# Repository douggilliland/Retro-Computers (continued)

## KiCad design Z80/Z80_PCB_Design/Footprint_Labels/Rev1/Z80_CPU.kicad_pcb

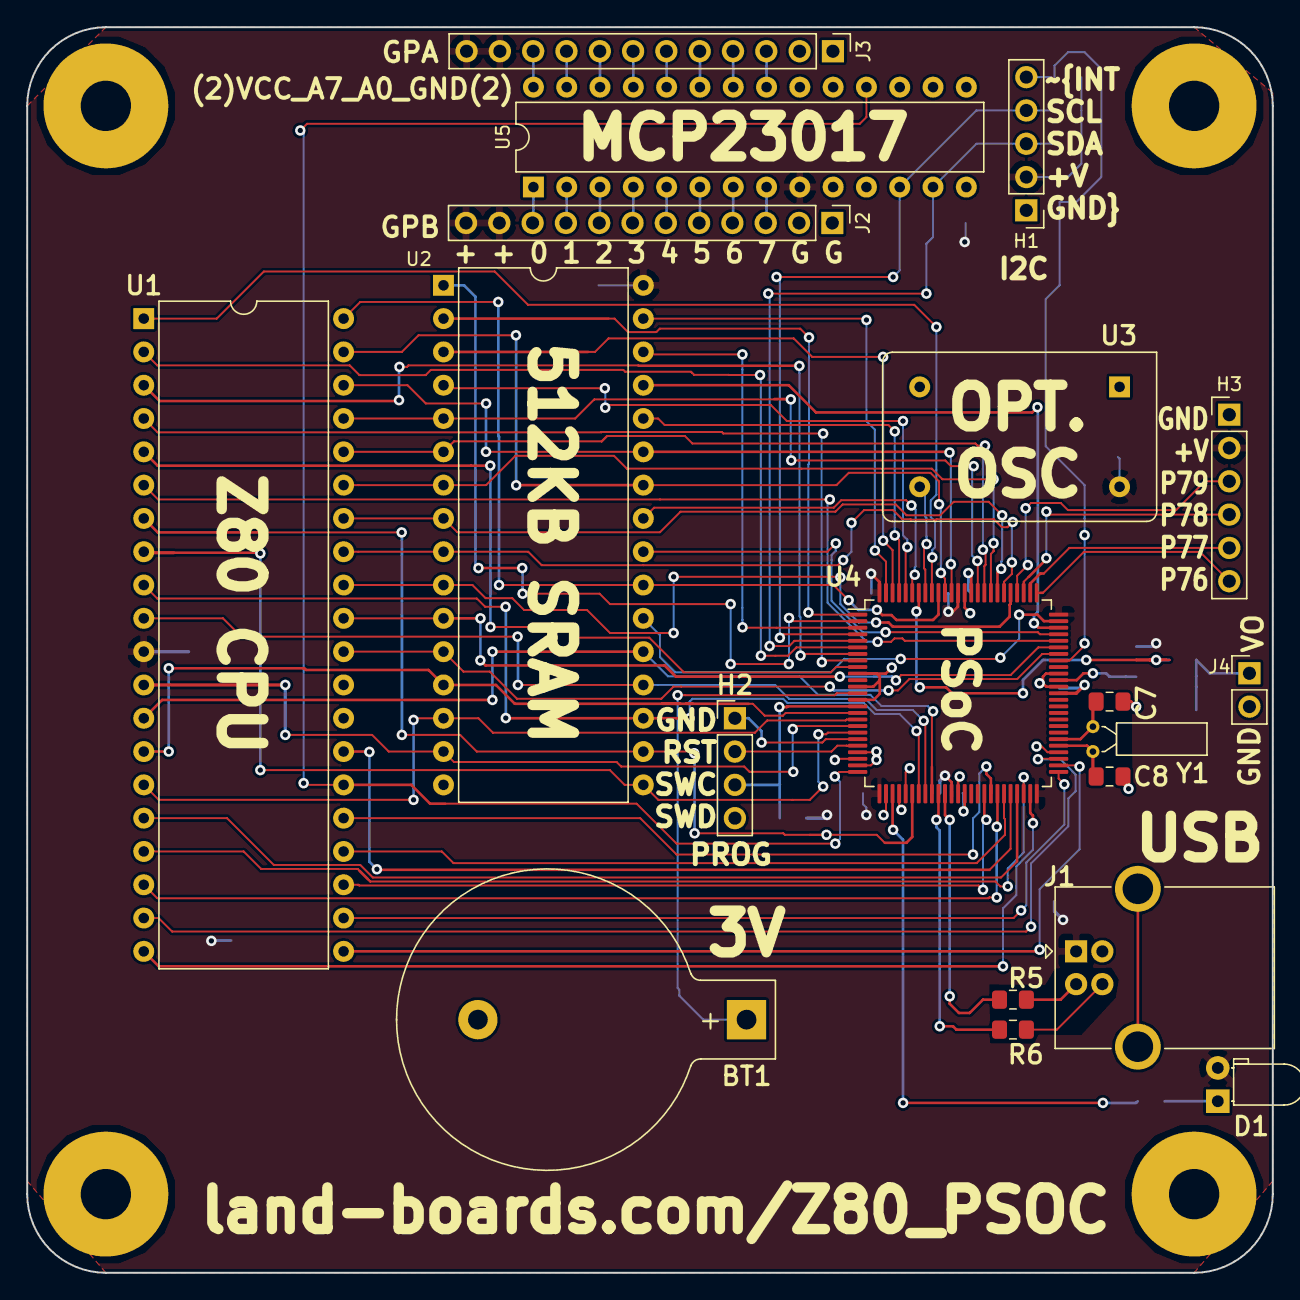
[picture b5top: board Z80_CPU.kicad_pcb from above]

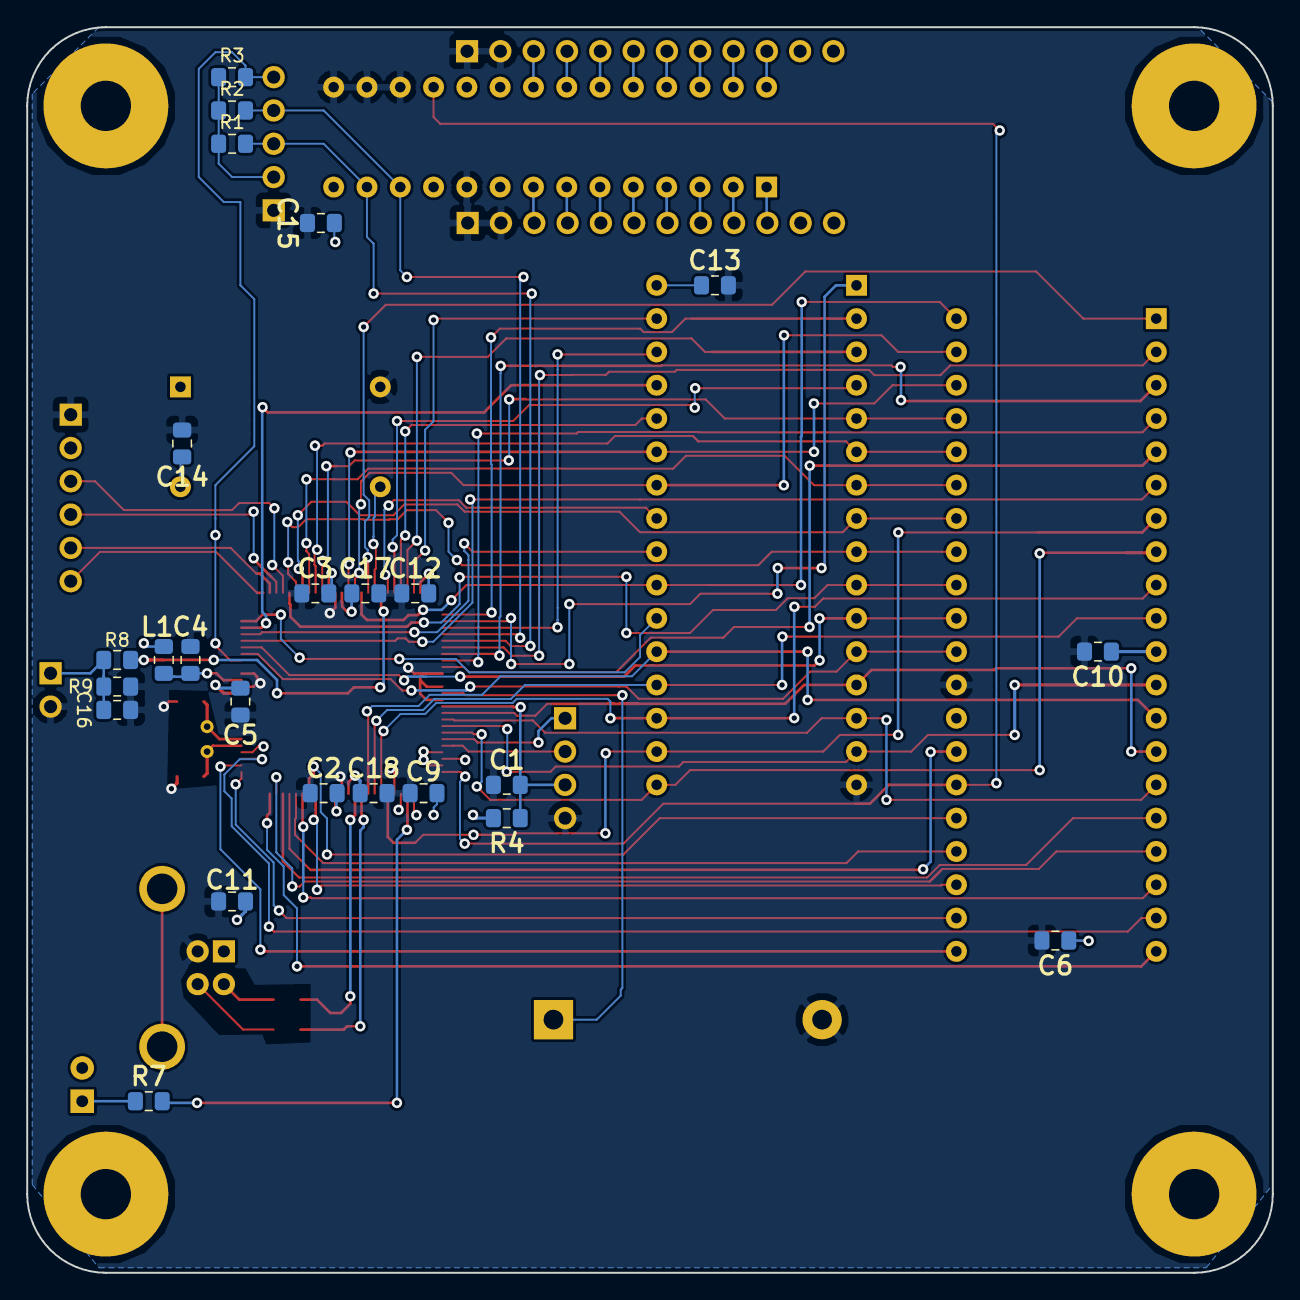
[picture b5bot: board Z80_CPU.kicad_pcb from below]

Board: 2 copper layers, 95.0 x 95.0 mm, 47 parts (24 on the bottom side), 92 nets.

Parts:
BT1: Battery_Cell; BatteryHolder_Keystone_103_1x20mm
C1, C6, C9, C10, C11, C12, C13, C14, C15, C17, C18: 0.1uF; C_0805_2012Metric_Pad1.15x1.40mm_HandSolder
C2, C3, C4, C5: 1uF; C_0805_2012Metric_Pad1.15x1.40mm_HandSolder
C7, C8, C16: 10pF; C_0805_2012Metric_Pad1.15x1.40mm_HandSolder
D1: LED_Small_ALT; LED_D3.0mm_Horizontal_O1.27mm_Z2.0mm
H1: Conn_01x05; PinHeader_1x05_P2.54mm_Vertical
H2: Conn_01x04; PinHeader_1x04_P2.54mm_Vertical
H3: Conn_01x06; PinHeader_1x06_P2.54mm_Vertical
J1: USB_B; USB_B_OST_USB-B1HSxx_Horizontal
J2, J3: Conn_01x12; PinHeader_1x12_P2.54mm_Vertical
J4: Conn_01x02; PinHeader_1x02_P2.54mm_Vertical
L1: ChipInd; L_0805_2012Metric_Pad1.15x1.40mm_HandSolder
MTG1, MTG2, MTG3: MTG_HOLE; MTG-6-32
MTG?1: MTG_HOLE; MTG-6-32
R1, R2, R3, R8, R9: 2.2K; R_0805_2012Metric_Pad1.15x1.40mm_HandSolder
R4: 3.9K; R_0805_2012Metric_Pad1.15x1.40mm_HandSolder
R5, R6: 22; R_0805_2012Metric_Pad1.15x1.40mm_HandSolder
R7: 330; R_0805_2012Metric_Pad1.15x1.40mm_HandSolder
U1: Z80CPU; DIP-40_W15.24mm
U2: AS6C4008; DIP-32_W15.24mm
U3: 4.9152 MHz; Oscillator_DIP-14
U4: CY8C5267AXI-LP051; TQFP-100_14x14mm_P0.5mm
U5: MCP23017_SP; DIP-28_W7.62mm
Y1: 32.768KHz; Crystal_C26-LF_D2.1mm_L6.5mm_Horizontal

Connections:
+5V: C6.2, C9.2, C10.2, C11.2, C12.2, C13.2, C14.2, C15.2, C17.2, C18.2, D1.2, H1.2, H3.2, J1.1, J2.11, J2.12, J3.11, J3.12, L1.2, R1.1, R2.1, R3.1, R4.1, U1.11, U2.32, U3.14, U4.26, U4.37, U4.50, U4.75, U4.88, U4.100, U5.9
/CPUA0: U1.30, U2.12, U4.69
/CPUA1: U1.31, U2.11, U4.70
/CPUA2: U1.32, U2.10, U4.80
/CPUA3: U1.33, U2.9, U4.81
/CPUA4: U1.34, U2.8, U4.82
/CPUA5: U1.35, U2.7, U4.83
/CPUA6: U1.36, U2.6, U4.84
/CPUA7: U1.37, U2.5, U4.85
/CPUA8: U1.38, U2.27, U4.89
/CPUA9: U1.39, U2.26, U4.90
/CPUA10: U1.40, U2.23, U4.91
/CPUA11: U1.1, U4.92
/CPUA12: U1.2, U4.6
/CPUA13: U1.3, U4.7
/CPUA14: U1.4, U4.8
/CPUA15: U1.5, U4.9
/CPUCLK: U1.6, U4.71
/CPUD0: U1.14, U2.13, U4.16
/CPUD1: U1.15, U2.14, U4.17
/CPUD2: U1.12, U2.15, U4.18
/CPUD3: U1.8, U2.17, U4.19
/CPUD4: U1.7, U2.18, U4.31
/CPUD5: U1.9, U2.19, U4.32
/CPUD6: U1.10, U2.20, U4.33
/CPUD7: U1.13, U2.21, U4.34
/DAC_OUT: R8.2, U4.94
/GPA0: J3.3, U5.21
/GPA1: J3.4, U5.22
/GPA2: J3.5, U5.23
/GPA3: J3.6, U5.24
/GPA4: J3.7, U5.25
/GPA5: J3.8, U5.26
/GPA6: J3.9, U5.27
/GPA7: J3.10, U5.28
/GPB0: J2.10, U5.1
/GPB1: J2.9, U5.2
/GPB2: J2.8, U5.3
/GPB3: J2.7, U5.4
/GPB4: J2.6, U5.5
/GPB5: J2.5, U5.6
/GPB6: J2.4, U5.7
/GPB7: J2.3, U5.8
/P76: H3.6, U4.76
/P77: H3.5, U4.77
/P78: H3.4, U4.78
/P79: H3.3, U4.79
/SCL: H1.4, R2.2, U4.4, U5.12
/SDA: H1.3, R1.2, U4.5, U5.13
/SRAMA11: U2.25, U4.95
/SRAMA12: U2.4, U4.96
/SRAMA13: U2.28, U4.97
/SRAMA14: U2.3, U4.98
/SRAMA15: U2.31, U4.99
/SRAMA16: U2.2, U4.1
/SRAMA17: U2.30, U4.3
/SRAMA18: U2.1, U4.2
/SWC: H2.2, U4.21
/SWD: H2.1, U4.20
/USB-DM: J1.2, R5.1
/USB-DP: J1.3, R6.1
/~BUSACK: U1.23, U4.42
/~BUSRQ: U1.25, U4.43
/~CPURD: U1.21, U4.52
/~CPURST: U1.26, U4.25, U5.18
/~CPUWR: U1.22, U4.51
/~HALT: U1.18, U4.44
/~I2CINT: H1.5, R3.2, U4.68
/~INT: U1.16, U4.47
/~IORQ: U1.20, U4.49
/~M1: U1.27, U4.46
/~MEMRD: U2.24, U4.72
/~MEMWR: U2.29, U4.73
/~MREQ: U1.19, U4.53
/~NMI: U1.17, U4.48
/~SRAMCS: U2.22, U4.74
/~WAIT: U1.24, U4.45
GND: BT1.2, C1.2, C2.2, C3.2, C4.2, C5.2, C6.1, C7.1, C8.1, C9.1, C10.1, C11.1, C12.1, C13.1, C14.1, C15.1, C16.1, C17.1, C18.1, H1.1, H2.4, H3.1, J1.4, J2.1, J2.2, J3.1, J3.2, J4.2, R9.1, U1.29, U2.16, U3.7, U4.10, U4.12, U4.14, U4.38, U4.64, U4.66, U4.87, U5.10, U5.15, U5.16, U5.17
unnamed: BT1.1, U4.13
unnamed: C1.1, H2.3, R4.2, U4.15
unnamed: C2.1, U4.39
unnamed: C3.1, U4.86
unnamed: C4.1, L1.1, U4.65
unnamed: C5.1, U4.63
unnamed: C7.2, U4.56, Y1.2
unnamed: C8.2, U4.55, Y1.1
unnamed: C16.2, J4.1, R8.1, R9.2
unnamed: D1.1, R7.1
unnamed: R5.2, U4.36
unnamed: R6.2, U4.35
unnamed: R7.2, U4.28
unnamed: U3.8, U4.93

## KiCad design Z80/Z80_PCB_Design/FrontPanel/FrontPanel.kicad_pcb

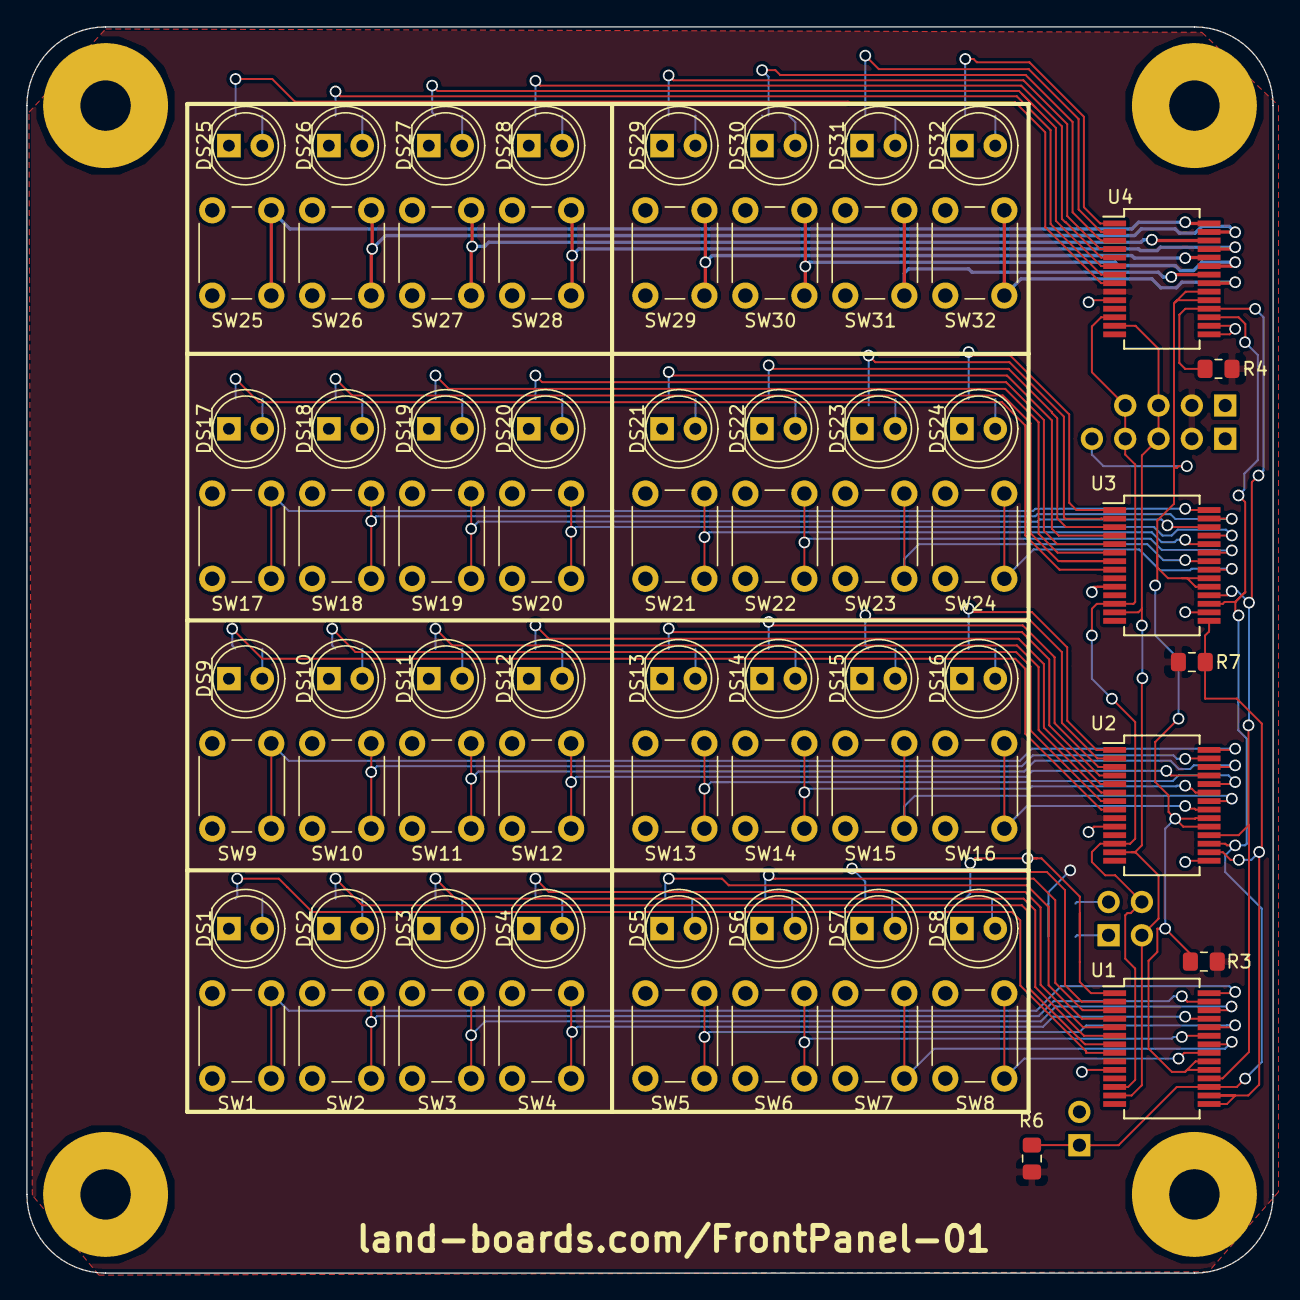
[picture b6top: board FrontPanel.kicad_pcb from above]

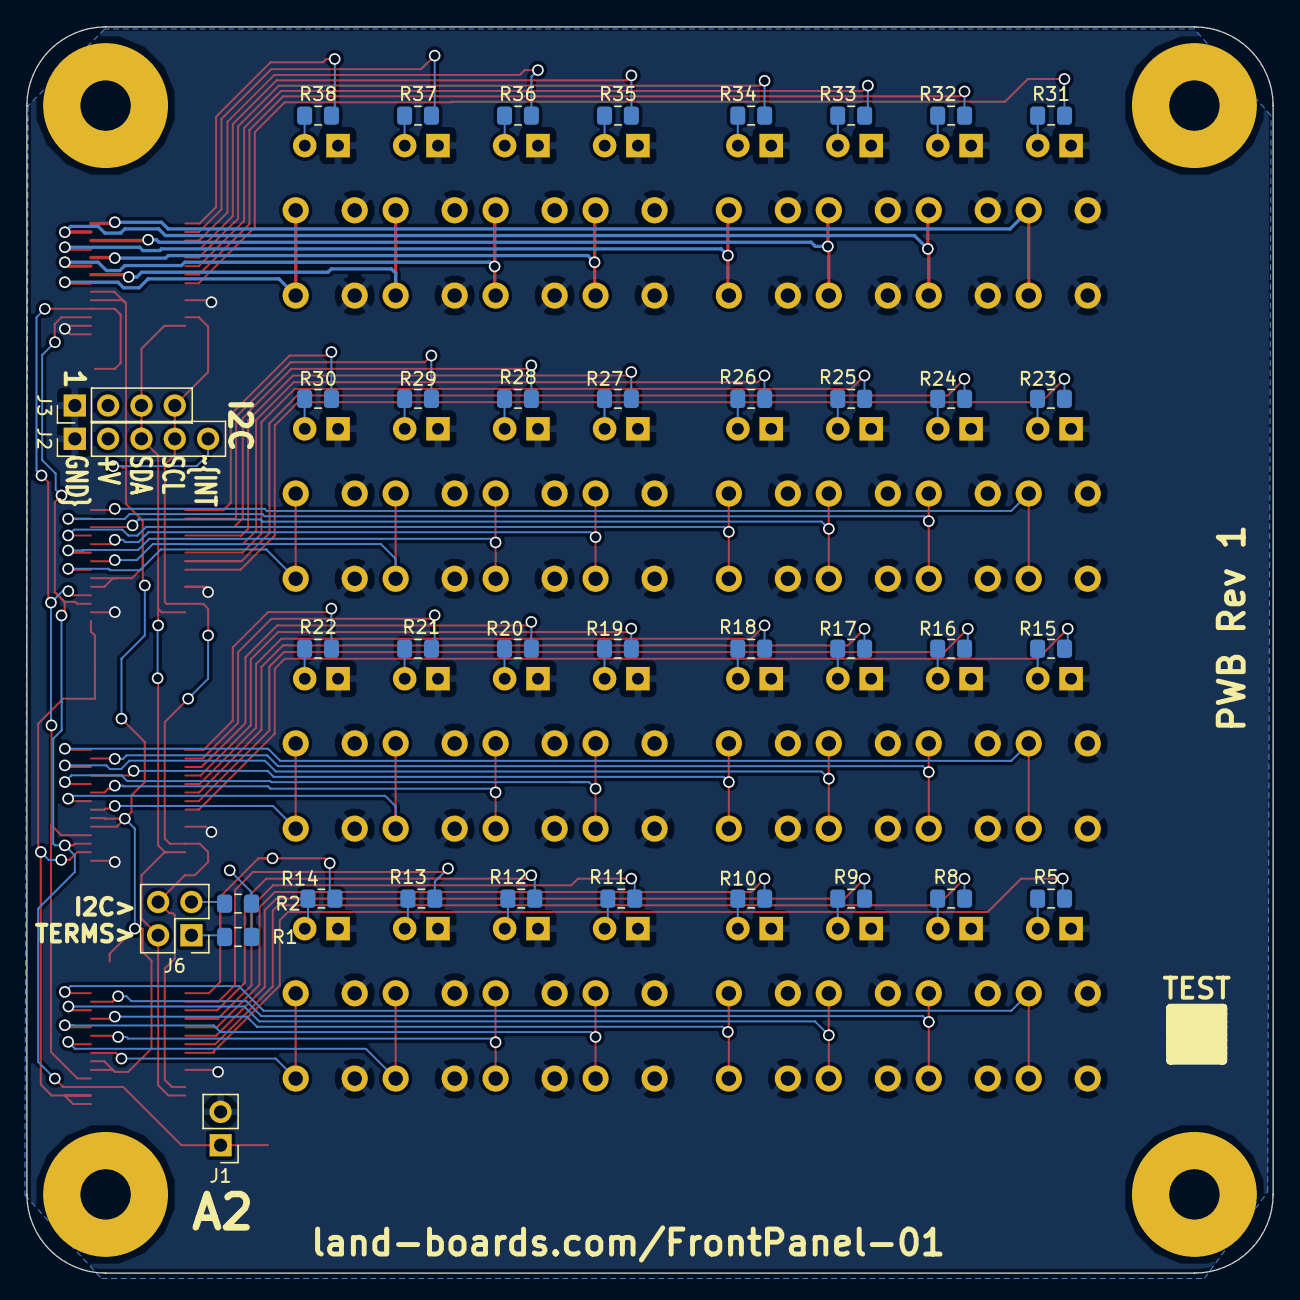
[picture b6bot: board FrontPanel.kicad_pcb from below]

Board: 2 copper layers, 95.0 x 95.0 mm, 115 parts (38 on the bottom side), 106 nets.

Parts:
DS1, DS2, DS3, DS4, DS5, DS6, DS7, DS8, DS9, DS10, DS11, DS12, DS13, DS14, DS15, DS16, DS17, DS18, DS19, DS20, DS21, DS22, DS23, DS24, DS25, DS26, DS27, DS28, DS29, DS30, DS31, DS32: LED; LED_D5.0mm
J1: Conn_01x02; PinHeader_1x02_P2.54mm_Vertical
J2: Conn_01x05; PinHeader_1x05_P2.54mm_Vertical
J3: CONN_4; PinHeader_1x04_P2.54mm_Vertical
J6: CONN_02X02; PinHeader_2x02_P2.54mm_Vertical
MTG1, MTG2, MTG3, MTG4: MTG_HOLE; MTG-6-32
R1, R2: 2.2K; R_0805_2012Metric_Pad1.15x1.40mm_HandSolder
R3, R4, R6, R7: 10K; R_0805_2012Metric_Pad1.15x1.40mm_HandSolder
R5, R8, R9, R10, R11, R12, R13, R14, R15, R16, R17, R18, R19, R20, R21, R22, R23, R24, R25, R26, R27, R28, R29, R30, R31, R32, R33, R34, R35, R36, R37, R38: 330; R_0805_2012Metric_Pad1.15x1.40mm_HandSolder
SW1, SW2, SW3, SW4, SW5, SW6, SW7, SW8, SW9, SW10, SW11, SW12, SW13, SW14, SW15, SW16, SW17, SW18, SW19, SW20, SW21, SW22, SW23, SW24, SW25, SW26, SW27, SW28, SW29, SW30, SW31, SW32: SW_Push; SW_PUSH_6mm
TEST: CONN_1; TEST_BLK-REAR
U1, U2, U3, U4: MCP23017-E/SS; SSOP-28_5.3x10.2mm_P0.65mm

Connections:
+5V: J2.2, J3.2, R1.2, R2.2, R3.1, R4.1, R6.2, R7.1, U1.9, U2.9, U3.9, U4.9
/A2: J1.1, R6.1, U1.17, U2.17, U3.17, U4.17
/PUPADR: R7.2, U1.15, U1.16, U2.16, U3.15
/PUPINT: J2.5, R3.2, U1.19, U1.20, U2.19, U2.20, U3.19, U3.20, U4.19, U4.20
/PUPRST: R4.2, U1.18, U2.18, U3.18, U4.18
/S1D0: SW8.2, U1.21
/S1D1: SW7.2, U1.22
/S1D2: SW6.2, U1.23
/S1D3: SW5.2, U1.24
/S1D4: SW4.2, U1.25
/S1D5: SW3.2, U1.26
/S1D6: SW2.2, U1.27
/S1D7: SW1.2, U1.28
/S2D0: SW16.2, U2.21
/S2D1: SW15.2, U2.22
/S2D2: SW14.2, U2.23
/S2D3: SW13.2, U2.24
/S2D4: SW12.2, U2.25
/S2D5: SW11.2, U2.26
/S2D6: SW10.2, U2.27
/S2D7: SW9.2, U2.28
/S3D0: SW24.2, U3.21
/S3D1: SW23.2, U3.22
/S3D2: SW22.2, U3.23
/S3D3: SW21.2, U3.24
/S3D4: SW20.2, U3.25
/S3D5: SW19.2, U3.26
/S3D6: SW18.2, U3.27
/S3D7: SW17.2, U3.28
/S4D0: SW32.2, U4.21
/S4D1: SW31.2, U4.22
/S4D2: SW30.2, U4.23
/S4D3: SW29.2, U4.24
/S4D4: SW28.2, U4.25
/S4D5: SW27.2, U4.26
/S4D6: SW26.2, U4.27
/S4D7: SW25.2, U4.28
/SCL: J2.4, J3.4, J6.4, U1.12, U2.12, U3.12, U4.12
/SDA: J2.3, J3.3, J6.2, U1.13, U2.13, U3.13, U4.13
GND: DS1.1, DS2.1, DS3.1, DS4.1, DS5.1, DS6.1, DS7.1, DS8.1, DS9.1, DS10.1, DS11.1, DS12.1, DS13.1, DS14.1, DS15.1, DS16.1, DS17.1, DS18.1, DS19.1, DS20.1, DS21.1, DS22.1, DS23.1, DS24.1, DS25.1, DS26.1, DS27.1, DS28.1, DS29.1, DS30.1, DS31.1, DS32.1, J1.2, J2.1, J3.1, SW1.1, SW2.1, SW3.1, SW4.1, SW5.1, SW6.1, SW7.1, SW8.1, SW9.1, SW10.1, SW11.1, SW12.1, SW13.1, SW14.1, SW15.1, SW16.1, SW17.1, SW18.1, SW19.1, SW20.1, SW21.1, SW22.1, SW23.1, SW24.1, SW25.1, SW26.1, SW27.1, SW28.1, SW29.1, SW30.1, SW31.1, SW32.1, U1.10, U2.10, U2.15, U3.10, U3.16, U4.10, U4.15, U4.16
unnamed: DS1.2, R5.1
unnamed: DS2.2, R8.1
unnamed: DS3.2, R9.1
unnamed: DS4.2, R10.1
unnamed: DS5.2, R11.1
unnamed: DS6.2, R12.1
unnamed: DS7.2, R13.1
unnamed: DS8.2, R14.1
unnamed: DS9.2, R15.1
unnamed: DS10.2, R16.1
unnamed: DS11.2, R17.1
unnamed: DS12.2, R18.1
unnamed: DS13.2, R19.1
unnamed: DS14.2, R20.1
unnamed: DS15.2, R21.1
unnamed: DS16.2, R22.1
unnamed: DS17.2, R23.1
unnamed: DS18.2, R24.1
unnamed: DS19.2, R25.1
unnamed: DS20.2, R26.1
unnamed: DS21.2, R27.1
unnamed: DS22.2, R28.1
unnamed: DS23.2, R29.1
unnamed: DS24.2, R30.1
unnamed: DS25.2, R31.1
unnamed: DS26.2, R32.1
unnamed: DS27.2, R33.1
unnamed: DS28.2, R34.1
unnamed: DS29.2, R35.1
unnamed: DS30.2, R36.1
unnamed: DS31.2, R37.1
unnamed: DS32.2, R38.1
unnamed: J6.1, R1.1
unnamed: J6.3, R2.1
unnamed: R5.2, U1.8
unnamed: R8.2, U1.7
unnamed: R9.2, U1.6
unnamed: R10.2, U1.5
unnamed: R11.2, U1.4
unnamed: R12.2, U1.3
unnamed: R13.2, U1.2
unnamed: R14.2, U1.1
unnamed: R15.2, U2.8
unnamed: R16.2, U2.7
unnamed: R17.2, U2.6
unnamed: R18.2, U2.5
unnamed: R19.2, U2.4
unnamed: R20.2, U2.3
unnamed: R21.2, U2.2
unnamed: R22.2, U2.1
unnamed: R23.2, U3.8
unnamed: R24.2, U3.7
unnamed: R25.2, U3.6
unnamed: R26.2, U3.5
unnamed: R27.2, U3.4
unnamed: R28.2, U3.3
unnamed: R29.2, U3.2
unnamed: R30.2, U3.1
unnamed: R31.2, U4.8
unnamed: R32.2, U4.7
unnamed: R33.2, U4.6
unnamed: R34.2, U4.5
unnamed: R35.2, U4.4
unnamed: R36.2, U4.3
unnamed: R37.2, U4.2
unnamed: R38.2, U4.1
